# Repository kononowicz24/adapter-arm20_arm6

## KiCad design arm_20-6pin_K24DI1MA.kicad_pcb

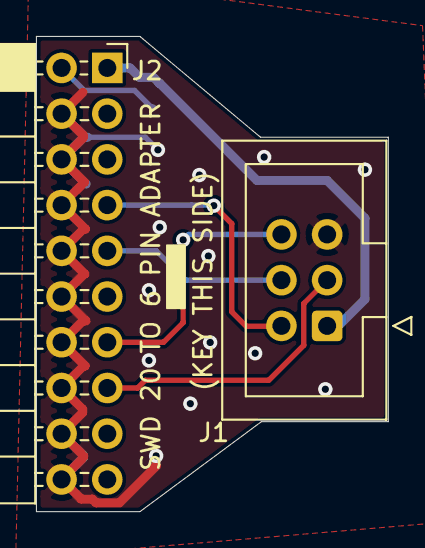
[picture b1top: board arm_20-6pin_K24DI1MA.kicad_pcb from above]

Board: 2 copper layers, 19.6 x 26.4 mm, 3 parts (1 on the bottom side), 7 nets.

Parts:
J1: Conn_02x03_Odd_Even; IDC-Header_2x03_P2.54mm_Vertical
J2: Conn_02x10_Odd_Even; PinSocket_2x10_P2.54mm_Horizontal
R1: R; R_0603_1608Metric

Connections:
/RESET: J1.3, J2.15
/SWCLK: J1.4, J2.9
/SWDIO: J1.2, J2.7
/SWO: J1.6, J2.13
/VTREF: J1.1, J2.1, R1.1
GND: J1.5, J2.4, J2.6, J2.8, J2.10, J2.12, J2.14, J2.16, J2.18, J2.20
unnamed: J2.2, R1.2

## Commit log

2023-09-26 Added all design files, cleaned up main folder, regenerated gerber and drill files, added SCH PDF.
